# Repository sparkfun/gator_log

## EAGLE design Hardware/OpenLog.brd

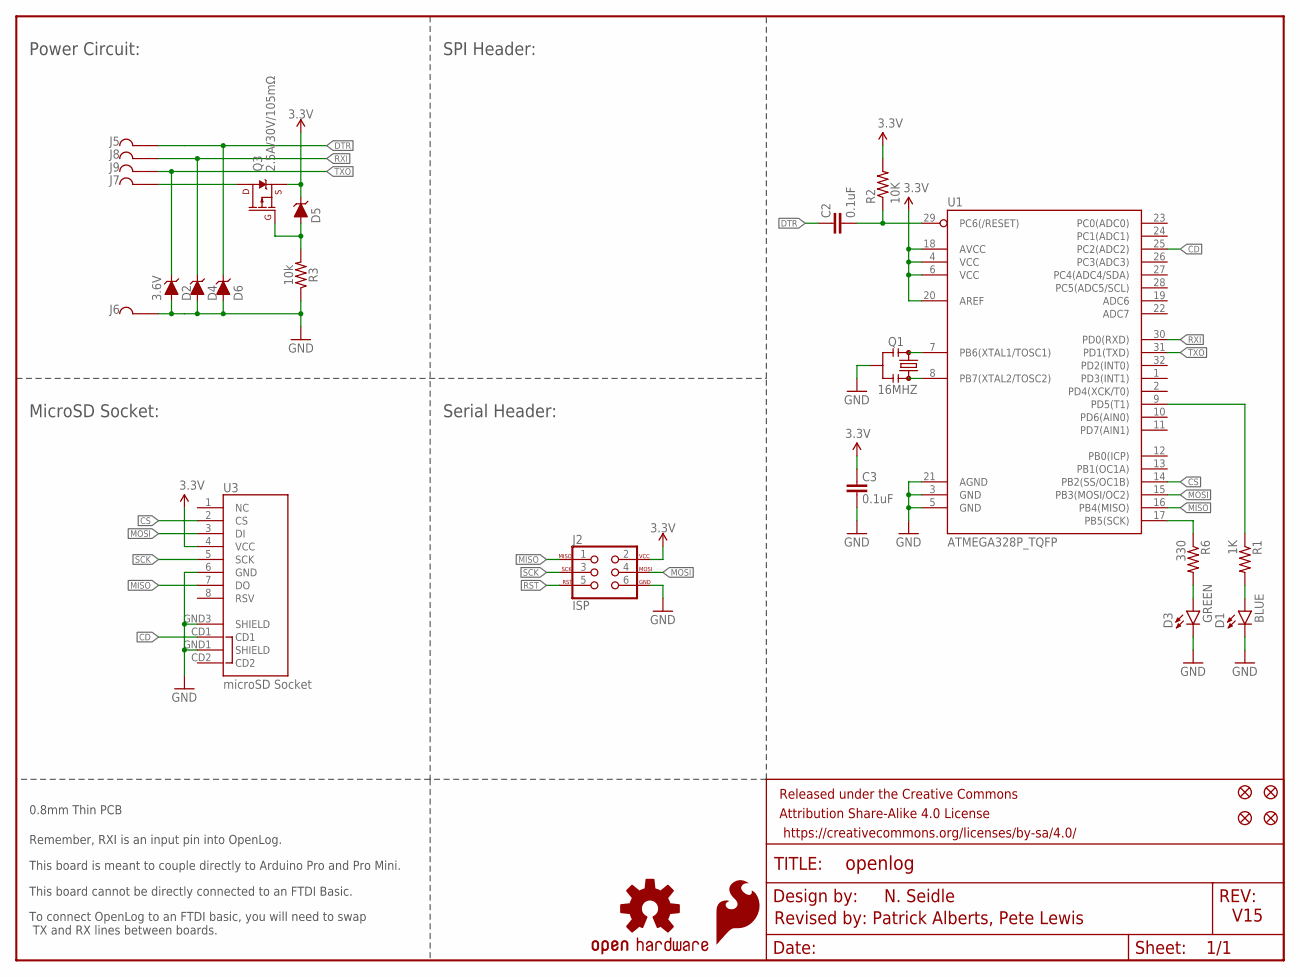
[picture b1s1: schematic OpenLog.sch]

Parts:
C2, C3: 0.1uF; 0603-CAP
D1: BLUE; LED-0603
D2, D4, D5, D6: 3.6V; SOD-323
D3: GREEN; LED-0603
FID1, FID2, FID3, FID4: FIDUCIALUFIDUCIAL; FIDUCIAL-MICRO
FRAME1: FRAME-LETTER; CREATIVE_COMMONS
J2: ISP; 2X3_TEST_POINTS
J5, J6, J7, J8, J9: GATORGATOR_MINI; GATOR_MINI
LOGO1: SFE_LOGO_FLAME.1_INCH; SFE_LOGO_FLAME_.1
LOGO2: OSHW-LOGOMINI; OSHW-LOGO-MINI
Q1: 16MHZ; RESONATOR-SMD
Q3: 2.5A/30V/105mΩ; SOT23-3
R1: 1K; 0603-RES
R2: 10K; 0603-RES
R3: 10k; 0603
R6: 330; 0603-RES
U1: ATMEGA328P_TQFP; TQFP32-08
U3: microSD Socket; MICROSD_1:1

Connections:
3.3V: C3.2, D5.C, J2.2, Q3.2 (S), R2.2, U1.4 (VCC), U1.6 (VCC), U1.18 (AVCC), U1.20 (AREF), U3.4 (VCC)
CD: U1.25 (PC2(ADC2)), U3.CD1
CS: U1.14 (PB2(SS/OC1B)), U3.2 (CS)
DTR: C2.2, D6.C, J5.P$2
GND: C3.1, D1.C, D2.A, D3.C, D4.A, D6.A, J2.6, J6.P$2, Q1.2, R3.1, U1.3 (GND), U1.5 (GND), U1.21 (AGND), U3.6 (GND), U3.GND1 (SHIELD), U3.GND3 (SHIELD)
MISO: J2.1, U1.16 (PB4(MISO)), U3.7 (DO)
MOSI: J2.4, U1.15 (PB3(MOSI/OC2)), U3.3 (DI)
unnamed: Q1.1, U1.8 (PB7(XTAL2/TOSC2))
unnamed: Q1.3, U1.7 (PB6(XTAL1/TOSC1))
unnamed: D1.A, R1.2
unnamed: R1.1, U1.9 (PD5(T1))
unnamed: D5.A, Q3.1 (G), R3.2
unnamed: J7.P$2, Q3.3 (D)
unnamed: D3.A, R6.2
RST: C2.1, J2.5, R2.1, U1.29 (PC6(/RESET))
RXI: D4.C, J8.P$2, U1.30 (PD0(RXD))
SCK: J2.3, R6.1, U1.17 (PB5(SCK)), U3.5 (SCK)
TXO: D2.C, J9.P$2, U1.31 (PD1(TXD))

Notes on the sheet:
Remember, RXI is an input pin into OpenLog.
This board is meant to couple directly to Arduino Pro and Pro Mini.
This board cannot be directly connected to an FTDI Basic.
To connect OpenLog to an FTDI basic, you will need to swap TX and RX lines between boards.
V15
N. Seidle
Revised by: Patrick Alberts, Pete Lewis
0.8mm Thin PCB
Power Circuit:
Serial Header:
MicroSD Socket:
SPI Header:

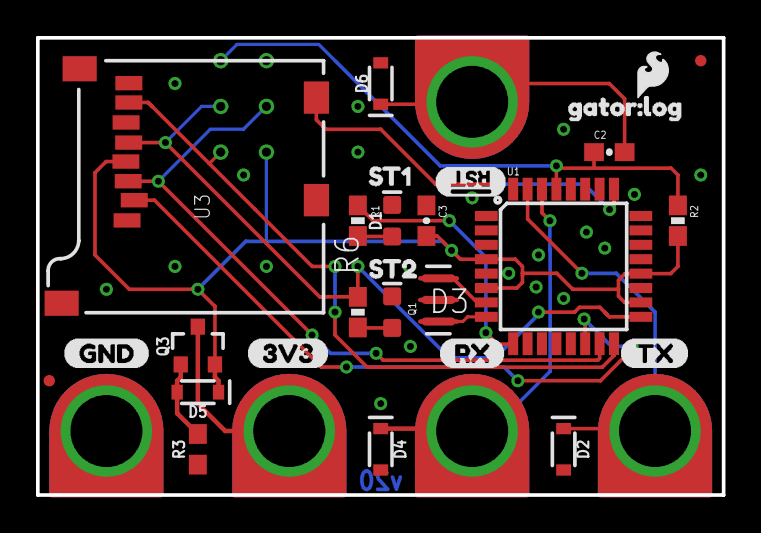
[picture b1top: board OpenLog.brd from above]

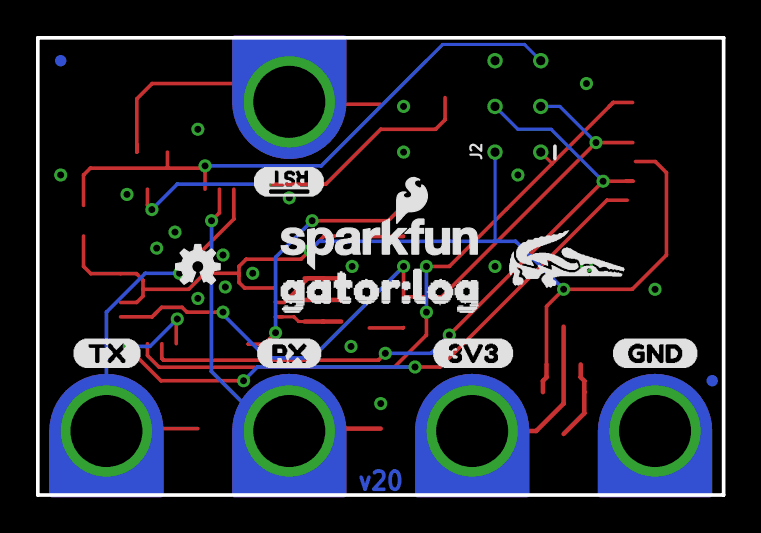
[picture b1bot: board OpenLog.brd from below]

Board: 2 copper layers, 38.1 x 25.4 mm, 45 parts (12 on the bottom side), 18 nets.

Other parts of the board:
U$1, U$2: #RST4
U$3, U$4: 3V32
U$5, U$6: GND3
U$7, U$8: RX0
U$9, U$10: TX1
U$11: GATOR#LOG6
U$12: GATOR#LOG5
U$13: SFE_LOGO_NAME_FLAME_.1
U$14: ST16
U$15: ST27
U$16: GATORBIT_FINAL_FOR_SILK#01_#1##JPG

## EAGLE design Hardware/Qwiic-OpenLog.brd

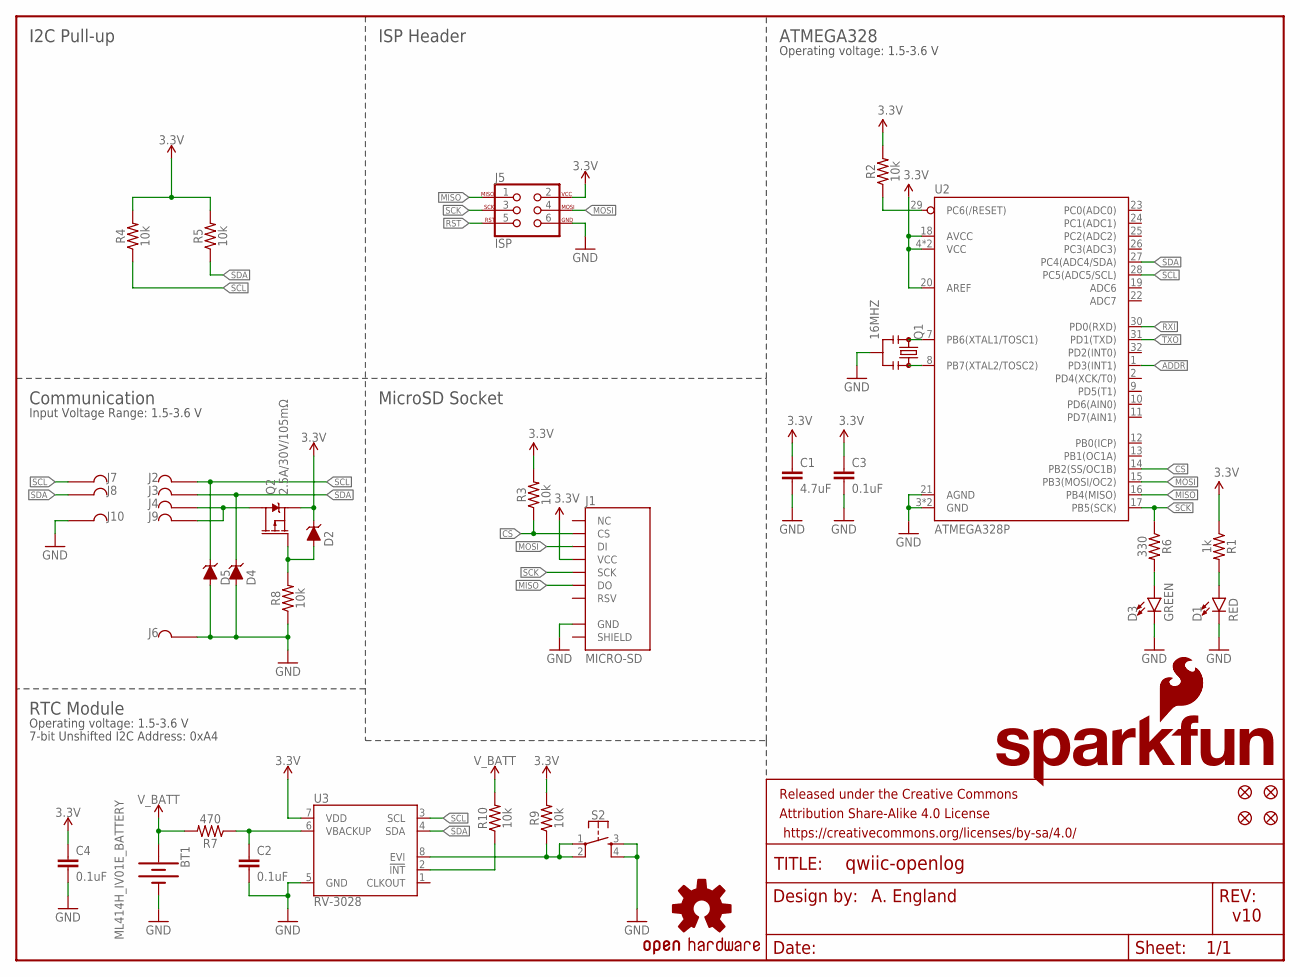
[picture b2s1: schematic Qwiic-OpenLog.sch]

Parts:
BT1: ML414H_IV01E_BATTERY; ML414H_IV01E
C1: 4.7uF; 0603
C2, C3, C4: 0.1uF; 0603
D1: RED; LED-0603
D2, D4, D5: 3.6V; SOD-323
D3: GREEN; LED-0603
FID1, FID2, FID3, FID4: FIDUCIALUFIDUCIAL; FIDUCIAL-MICRO
FRAME1: FRAME-LETTER; CREATIVE_COMMONS
J1: MICRO-SD; MICRO-SD-SOCKET
J2, J3, J4, J6, J7, J8, J9, J10: GATORGATOR_MINI; GATOR_MINI
J5: ISP; 2X3_TEST_POINTS
LOGO1: SFE_LOGO_FLAME.1_INCH; SFE_LOGO_FLAME_.1
LOGO2: OSHW-LOGOMINI; OSHW-LOGO-MINI
LOGO4: SFE_LOGO_NAME_FLAME.1_INCH; SFE_LOGO_NAME_FLAME_.1
Q1: 16MHZ; RESONATOR-SMD
Q2: 2.5A/30V/105mΩ; SOT23-3
R1: 1k; 0603
R2, R3, R4, R5, R8, R9, R10: 10k; 0603
R6: 330; 0603
R7: 470; 0603
S2: MOMENTARY-SWITCH-SPST-2-SMD-5.2MM-TALL; TACTILE_SWITCH_SMD_5.2MM
U2: ATMEGA328P; TQFP32-08
U3: RV-3028

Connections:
3.3V: C1.1, C3.1, C4.1, D2.C, J1.VCC, J5.2, Q2.2 (S), R1.1, R2.2, R3.2, R4.2, R5.2, R9.2, U2.4 (VCC), U2.6 (VCC), U2.18 (AVCC), U2.20 (AREF), U3.7 (VDD)
!RST: R10.1, U3.2 (!INT)
ADDR: U2.1 (PD3(INT1))
CS: J1.CS, R3.1, U2.14 (PB2(SS/OC1B))
GND: BT1.-, C1.2, C2.2, C3.2, C4.2, D1.C, D3.C, D4.A, D5.A, J1.GND, J5.6, J6.P$2, J10.P$2, Q1.2, R8.1, S2.3, S2.4, U2.3 (GND), U2.5 (GND), U2.21 (AGND), U3.5 (GND)
MISO: J1.DO, J5.1, U2.16 (PB4(MISO))
MOSI: J1.DI, J5.4, U2.15 (PB3(MOSI/OC2))
unnamed: Q1.1, U2.8 (PB7(XTAL2/TOSC2))
unnamed: Q1.3, U2.7 (PB6(XTAL1/TOSC1))
unnamed: D1.A, R1.2
unnamed: J4.P$2, J9.P$2, Q2.3 (D)
unnamed: D2.A, Q2.1 (G), R8.2
unnamed: D3.A, R6.2
unnamed: R9.1, S2.1, S2.2, U3.8 (EVI)
RST: J5.5, R2.1, U2.29 (PC6(/RESET))
RXI: U2.30 (PD0(RXD))
SCK: J1.SCLK (SCK), J5.3, R6.1, U2.17 (PB5(SCK))
SCL: D5.C, J2.P$2, J7.P$2, R4.1, U2.28 (PC5(ADC5/SCL)), U3.3 (SCL)
SDA: D4.C, J3.P$2, J8.P$2, R5.1, U2.27 (PC4(ADC4/SDA)), U3.4 (SDA)
TXO: U2.31 (PD1(TXD))
VBACKUP: C2.1, R7.1, U3.6 (VBACKUP)
V_BATT: BT1.+, R7.2, R10.2

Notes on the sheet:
v10
A. England
I2C Pull-up
Communication
MicroSD Socket
ISP Header
RTC Module
Operating voltage: 1.5-3.6 V
7-bit Unshifted I2C Address: 0xA4
ATMEGA328
Input Voltage Range: 1.5-3.6 V

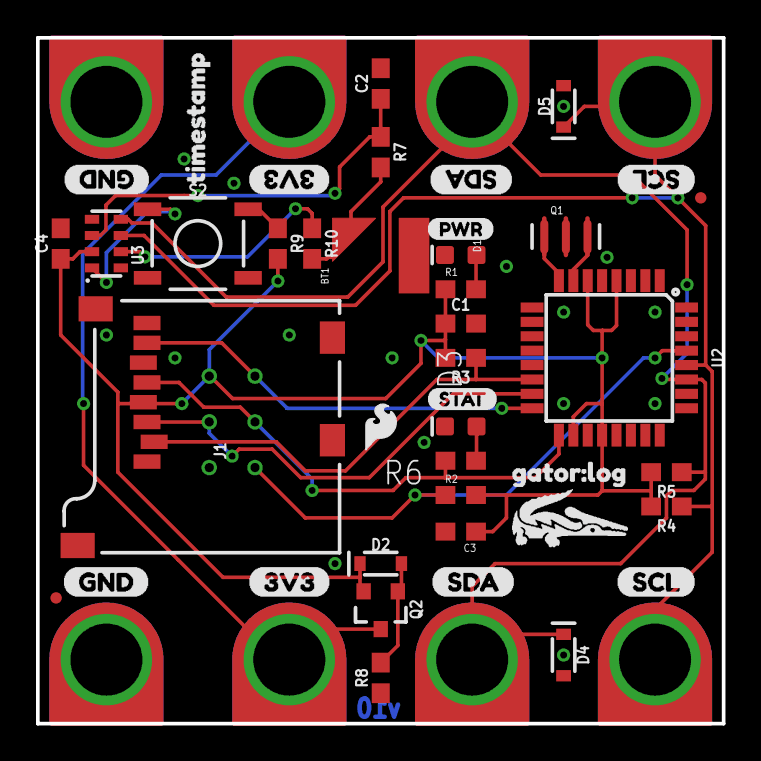
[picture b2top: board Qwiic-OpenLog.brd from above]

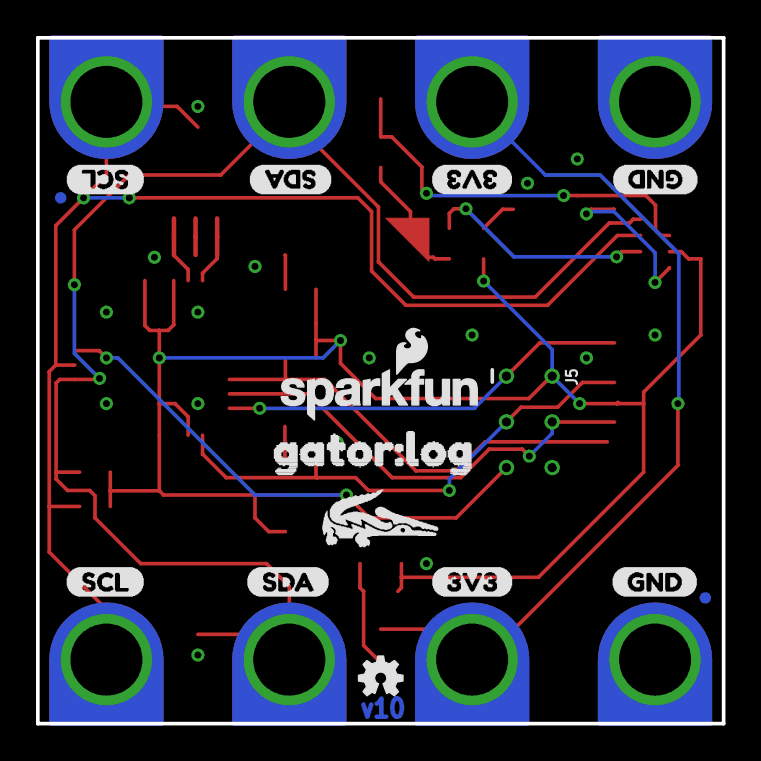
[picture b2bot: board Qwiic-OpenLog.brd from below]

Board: 2 copper layers, 38.1 x 38.1 mm, 67 parts (15 on the bottom side), 19 nets.

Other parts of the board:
U$1, U$3, U$12, U$15: 3V33
U$2, U$10, U$11, U$23: GND0
U$4, U$7, U$13, U$16: SDA1
U$5, U$6, U$14, U$18: SCL2
U$8, U$21: GATORBIT_FINAL_FOR_SILK#01#PNG
U$9: PWR-()-03
U$17: STAT0
U$19: TIMESTAMP0
U$20: GATOR#LOG3
U$22: ORDERING_INSTRUCTIONS
U$24: GATOR#LOG0

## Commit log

2019-02-22 initial commit, starting layout
2019-02-25 initial layout completed, needs silk
2019-02-25 adding RTC
2019-02-25 updating silk, adding rtc
2019-02-27 updating silk
2019-02-28 adding protection circuitry
2019-02-28 finalizing silk and schematic before design review
2019-03-01 engineer run of checklist
2019-04-16 pre design review for reds
2019-04-19 updating to RV-3028
2019-04-23 pre reds review changes
2019-04-30 post qc run of checklist
2019-04-30 centering silk
2019-04-30 panel
2019-06-04 changing name of file
2019-07-17 changing to Serial log
2019-07-17 serial changes, pre design review
2019-07-17 post checklist changes
2019-09-04 Update to correct product
    Folders and files for firmware still need to be modified.
2019-09-05 renaming firmware

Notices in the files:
parts and their libraries:
SparkFun-Connectors: Licensing: Creative Commons ShareAlike 4.0 International - https://creativecommons.org/licenses/by-sa/4.0
SparkFun-Aesthetics: Released under the Creative Commons Attribution Share-Alike 4.0 License
SparkFun-Aesthetics: https://creativecommons.org/licenses/by-sa/4.0
